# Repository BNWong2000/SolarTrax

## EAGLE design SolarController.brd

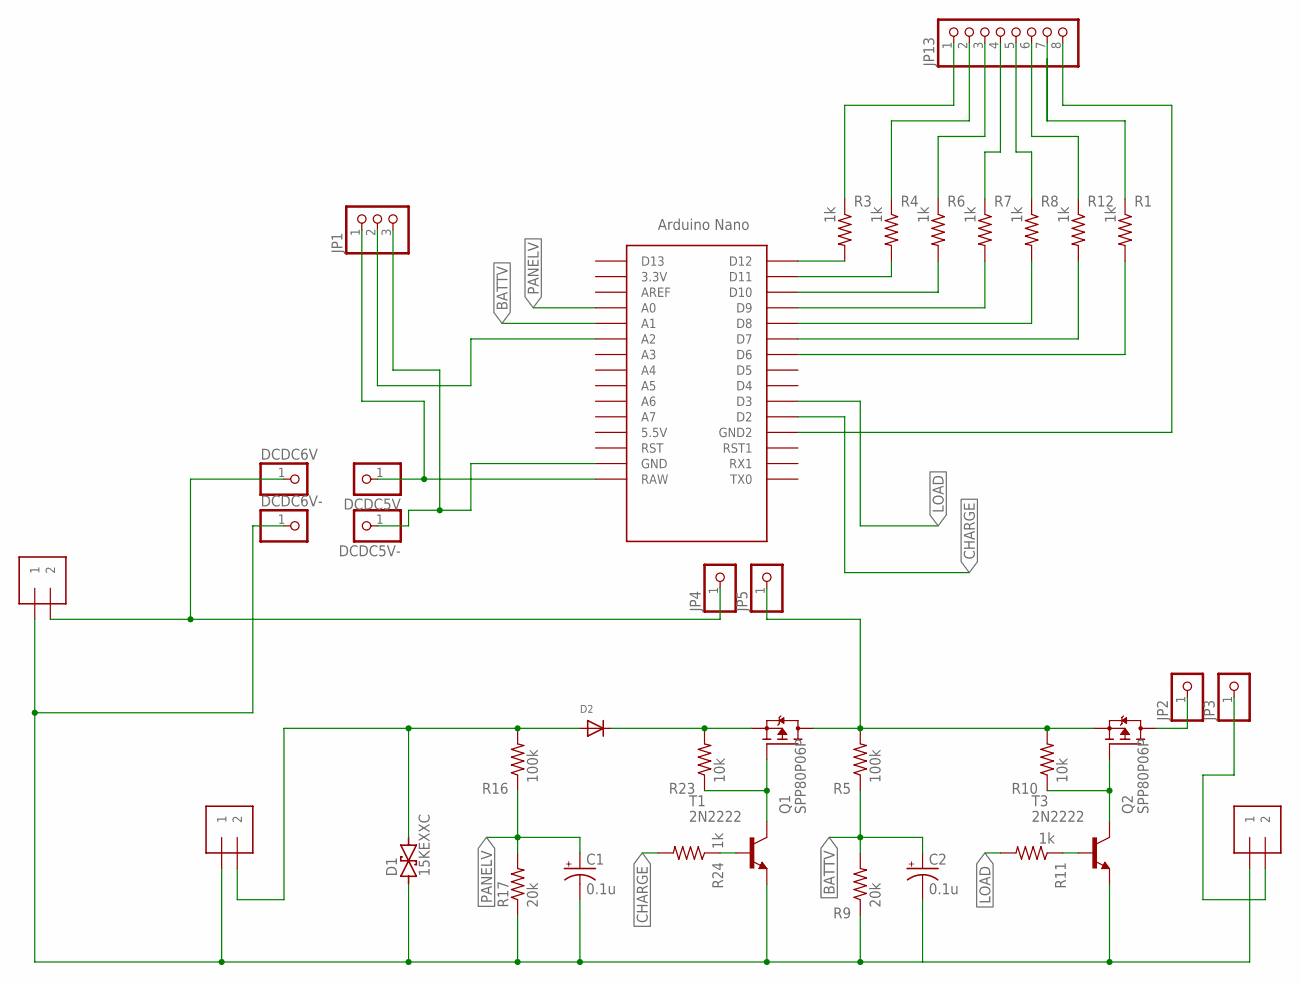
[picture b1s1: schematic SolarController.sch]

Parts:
BATTERY: 1X2-3.5MM
C1, C2: 0.1u; B45181B
D1: 15KEXXC; CB429-17
D2: DIODEDO-1N4148; DO-1N4148
DCDC5V, DCDC5V-, DCDC6V, DCDC6V-: PINHD-1X1CB; 1X01-CLEANBIG
JP1: PINHD-1X3CB; 1X03-CLEANBIG
JP2, JP3, JP4, JP5: PINHD-1X1CB; 1X01-CLEANBIG
JP13: PINHD-1X8BIG; 1X08-BIG
LOAD: 1X2-3.5MM
PANEL: 1X2-3.5MM
Q1, Q2: SPP80P06P; TO220
R1, R3, R4, R6, R7, R8, R11, R12, R24: 1k; 0207/9
R5, R16: 100k; 0207/9
R9, R17: 20k; 0207/9
R10, R23: 10k; 0207/9
T1, T3: 2N2222; TO92-EBC-OVAL
U$1: NANO

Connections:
BATTV: C2.+, R5.1, R9.2, U$1.A1
CHARGE: R24.2, U$1.D2
GND: BATTERY.1, C1.-, C2.-, D1.A (1), DCDC6V-.1, LOAD.1, PANEL.1, R9.1, R17.1, T1.E, T3.E
LOAD: R11.2, U$1.D3
unnamed: BATTERY.2, DCDC6V.1, JP4.1
unnamed: DCDC5V-.1, JP1.3, U$1.GND
unnamed: JP3.1, LOAD.2
unnamed: JP2.1, Q2.2 (D)
unnamed: D1.C (2), D2.A, PANEL.2, R16.2
unnamed: JP13.1, R3.1
unnamed: D2.C, Q1.3 (S), R23.2
unnamed: Q1.1 (G), R23.1, T1.C
unnamed: R24.1, T1.B
unnamed: JP5.1, Q1.2 (D), Q2.3 (S), R5.2, R10.2
unnamed: JP1.2, U$1.A2
unnamed: Q2.1 (G), R10.1, T3.C
unnamed: R11.1, T3.B
unnamed: DCDC5V.1, JP1.1, U$1.RAW
unnamed: JP13.2, R4.1
unnamed: JP13.3, R6.1
unnamed: JP13.4, R7.1
unnamed: JP13.5, R8.1
unnamed: JP13.6, R12.1
unnamed: JP13.7, R1.1
unnamed: JP13.8, U$1.GND1 (GND2)
unnamed: R3.2, U$1.D12
unnamed: R4.2, U$1.D11
unnamed: R6.2, U$1.D10
unnamed: R7.2, U$1.D9
unnamed: R8.2, U$1.D8
unnamed: R12.2, U$1.D7
unnamed: R1.2, U$1.D6
PANELV: C1.+, R16.1, R17.2

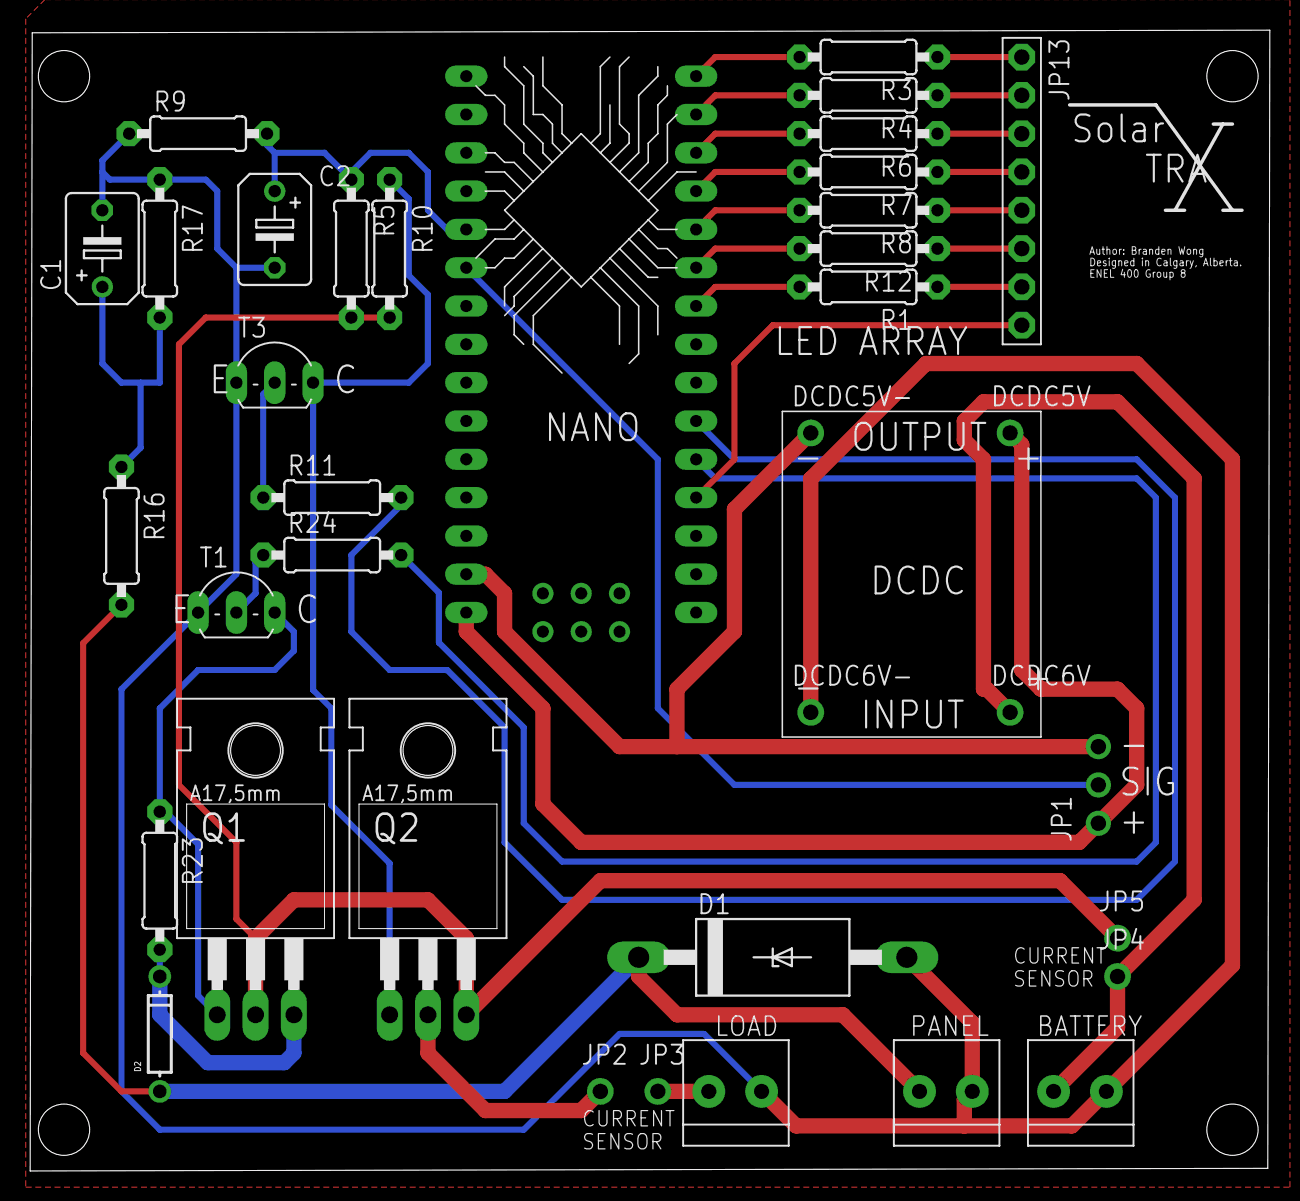
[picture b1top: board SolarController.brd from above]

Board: 2 copper layers, 82.2 x 75.6 mm, 37 parts (0 on the bottom side), 33 nets.

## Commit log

2020-04-08 Add files via upload
    Added PCB and schematic EAGLE files
